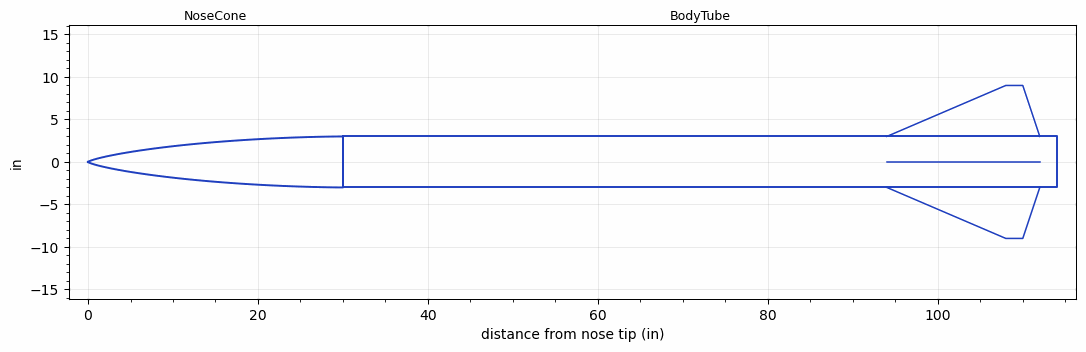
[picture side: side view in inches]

<RASAeroDocument>
 <FileVersion>2</FileVersion>
 <RocketDesign>
  <NoseCone>
   <Length>30</Length>
   <Diameter>6</Diameter>
   <Shape>LV-Haack</Shape>
   <Location>0</Location>
  </NoseCone>
  <BodyTube>
   <Length>84</Length>
   <Diameter>6</Diameter>
   <Location>30</Location>
   <Fin>
    <Count>4</Count>
    <Chord>18</Chord>
    <Span>6</Span>
    <SweepDistance>14</SweepDistance>
    <TipChord>2</TipChord>
    <Thickness>0.5</Thickness>
    <Location>20</Location>
    <AirfoilSection>Rounded</AirfoilSection>
   </Fin>
  </BodyTube>
  <Surface>Smooth (Zero Roughness)</Surface>
  <ModifiedBarrowman>False</ModifiedBarrowman>
  <Turbulence>False</Turbulence>
  <UseBooster1>False</UseBooster1>
  <UseBooster2>False</UseBooster2>
 </RocketDesign>
 <LaunchSite>
  <Altitude>0</Altitude>
  <Pressure>0</Pressure>
  <RodAngle>0</RodAngle>
  <RodLength>4</RodLength>
  <Temperature>74</Temperature>
  <WindSpeed>0</WindSpeed>
 </LaunchSite>
 <Recovery>
  <Altitude1>1000</Altitude1>
  <Altitude2>1000</Altitude2>
  <DeviceType1>None</DeviceType1>
  <DeviceType2>None</DeviceType2>
  <Event1>False</Event1>
  <Event2>False</Event2>
  <Size1>1</Size1>
  <Size2>1</Size2>
  <EventType1>None</EventType1>
  <EventType2>None</EventType2>
  <CD1>1.33</CD1>
  <CD2>1.33</CD2>
 </Recovery>
 <SimulationList>
  <Simulation>
   <SustainerLaunchWt>180</SustainerLaunchWt>
   <SustainerNozzleDiameter>4.25</SustainerNozzleDiameter>
   <SustainerCG>55</SustainerCG>
   <SustainerIgnitionDelay>0</SustainerIgnitionDelay>
   <Booster1SeparationDelay>0</Booster1SeparationDelay>
   <Booster1IgnitionDelay>0</Booster1IgnitionDelay>
   <IncludeBooster1>False</IncludeBooster1>
   <Booster2Delay>0</Booster2Delay>
   <IncludeBooster2>False</IncludeBooster2>
  </Simulation>
 </SimulationList>
</RASAeroDocument>
